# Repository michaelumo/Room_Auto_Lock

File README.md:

# Room_Auto_Lock
Locking up your room with esp8266 for some privacy

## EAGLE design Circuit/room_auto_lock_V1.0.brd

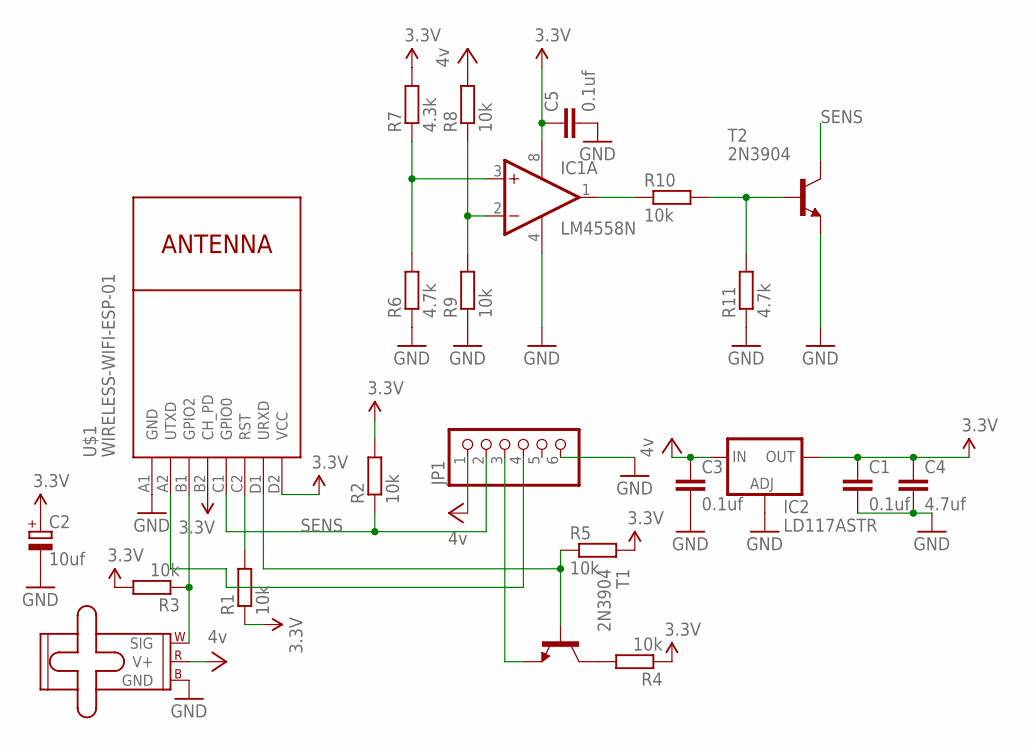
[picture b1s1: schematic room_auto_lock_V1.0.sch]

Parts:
C1, C3, C5: 0.1uf; C0805
C2: 10uf; E2,5-6
C4: 4.7uf; C1206K
IC1: LM4558N; DIL08
IC2: LD117ASTR; SOT223
JP1: PINHD-1X6; 1X06
M1: SMALL_SERVO; 1X03
R1, R2, R3, R4, R5: 10k; M2012
R6: 4.7k; 0207/2V
R7: 4.3k; 0207/2V
R8, R9, R10: 10k; R1206
R11: 4.7k; 0207/10
T1, T2: 2N3904; TO92
U$1: WIRELESS-WIFI-ESP-01

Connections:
3.3V: C1.1, C2.+, C4.1, C5.1, IC1.8 (V+), IC2.4 (OUT), R1.1, R2.2, R3.2, R4.1, R5.2, R7.2, U$1.B2 (CH_PD), U$1.D2 (VCC)
GND: C1.2, C2.-, C3.2, C4.2, C5.2, IC1.4 (V-), IC2.1 (ADJ), JP1.6, M1.3 (GND), R6.1, R9.1, R11.1, T2.3 (E), U$1.A1 (GND)
unnamed: M1.1 (SIG), R3.1, U$1.B1 (GPIO2)
unnamed: R1.2, U$1.C2 (RST)
unnamed: R5.1, T1.2 (B), U$1.D1 (URXD)
unnamed: JP1.4, U$1.A2 (UTXD)
unnamed: R4.2, T1.1 (C)
unnamed: JP1.3, T1.3 (E)
unnamed: IC1.2 (-IN), R8.1, R9.2
unnamed: IC1.3 (+IN), R6.2, R7.1
unnamed: IC1.1 (OUT), R10.1
unnamed: R10.2, R11.2, T2.2 (B)
SENS: JP1.2, R2.1, T2.1 (C), U$1.C1 (GPIO0)
VCC: C3.1, IC2.3 (IN), JP1.1, M1.2 (V+), R8.2

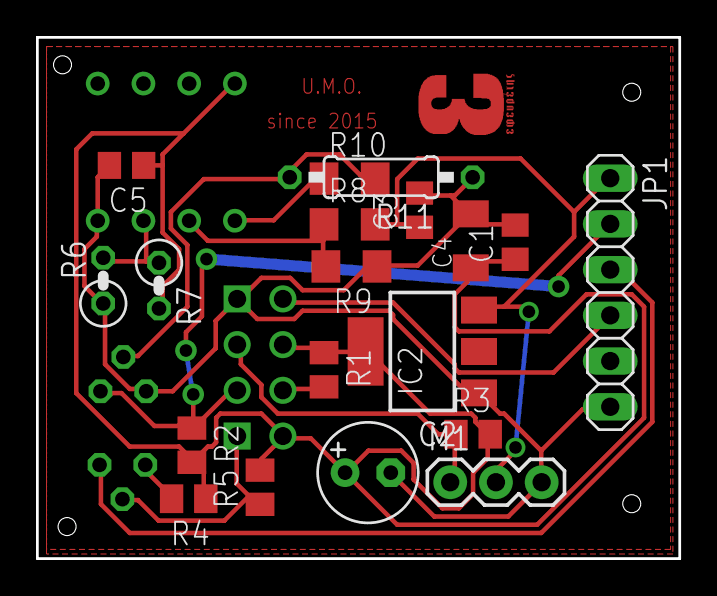
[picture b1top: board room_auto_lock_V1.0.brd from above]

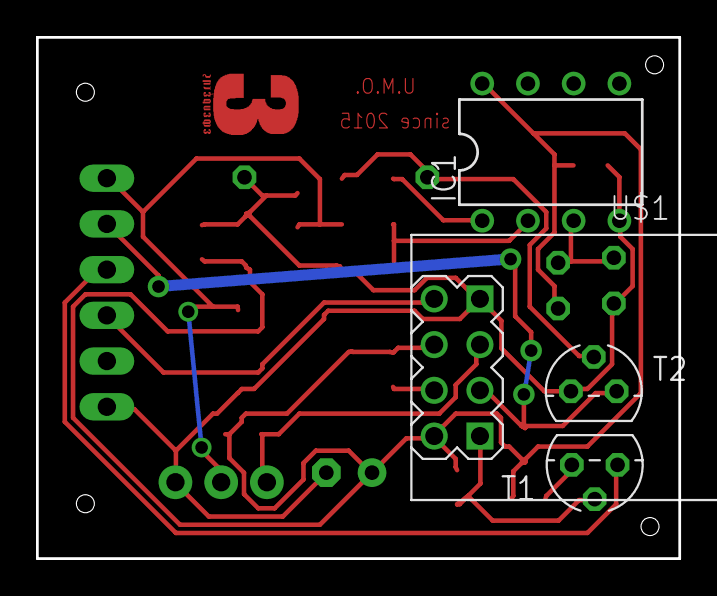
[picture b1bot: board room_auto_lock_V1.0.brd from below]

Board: 2 copper layers, 35.7 x 29.0 mm, 23 parts (4 on the bottom side), 14 nets.

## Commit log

2018-03-02 first_commit
2018-03-02 added_some_pictures

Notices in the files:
parts and their libraries:
SparkFun-Electromechanical: Licensing: Creative Commons ShareAlike 4.0 International - https://creativecommons.org/licenses/by-sa/4.0
diy-modules: Released under the Creative Commons Attribution 4.0 International License: http://creativecommons.org/licenses/by/4.0
